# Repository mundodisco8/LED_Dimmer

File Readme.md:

# Gruffalo Fairy Light Dimmer

A simple LED light dimmer. My kids love fairy lights, but the ones we have are too bright to use them as sleep lights so I thought about churning up a quick PWM dimmer for them.

It's a simple project with simple goals:

* Do some electronics. I won't get the Noble prize on electronics for this one.
  * Subgoal: doing something in the incredibly sexy [After Dark](https://blog.oshpark.com/2019/10/10/introducing-our-after-dark-black-fr-4-service/) finish from OSH Park.
* Play with the Silicon Labs toolchain. I don't have any FW on my Github.
* Work with encoders. They are tactile and they are nice!
* Think a bit on user interfaces that children can use.
* See how far I can get without getting sued for copyright infringement.

The design acts as a motherboard for another of my projects, a [breakout board for the BGM220P BLE Module](https://github.com/mundodisco8/BGM220P-Breakout).

This is more or less how it looks like. The renders are done with pcb2blender, and it doesn't handle transparent soldermasks yet, so it's not showing the underlying copper base.

## Working with this project.

It has two elements:

* The hardware is included as a KiCad project. All the files needed are in the `hardware` folder. Make sure you read the [`Readme.md`](hardware/Readme.md) file present there if you want to open it or modify something.
* The firmware is provided as a Simplicity Studio project (Silicon Labs' IDE). You can find it in the `src` folder. Like the HW project, check the [`Readme.md`](src/readme.md) file to get more details about it.

## Tools I'm Using / Stuff I'm Stealing.

Made with:

* KiCad for the HW design, Simplicity Studio / VS Code for the Firmware.
* Unity for unit testing.
* Inkscape, for the art manipulation.
* Fusion360, for 3D model generation, as a source for my Fab layers and for the enclosure.
* Blender + [pcb2blender](https://github.com/30350n/pcb2blender), to generate my renders.
* I'm using [KiBot](https://github.com/INTI-CMNB/KiBot) as the main tool in my CI/CD pipeline.
* I used the Pacifico font in some text elements in the PCB ([link](https://fonts.google.com/specimen/Pacifico))

Things I definitely didn't do:

* The art, taken from [certain children's book authors](https://www.gruffalo.com/).

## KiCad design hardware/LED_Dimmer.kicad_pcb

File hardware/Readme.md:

# Readme

## LED Dimmer PCB

List of things that are interesting to know in order to work with this project.

* This commit uses KiCad 8.0.5
* It uses an unusual font for some text elements. It's Pacifico ([can be obtained here](https://fonts.google.com/specimen/Pacifico), and a copy is left in the `resources/fonts` folder as KiBot needs it).

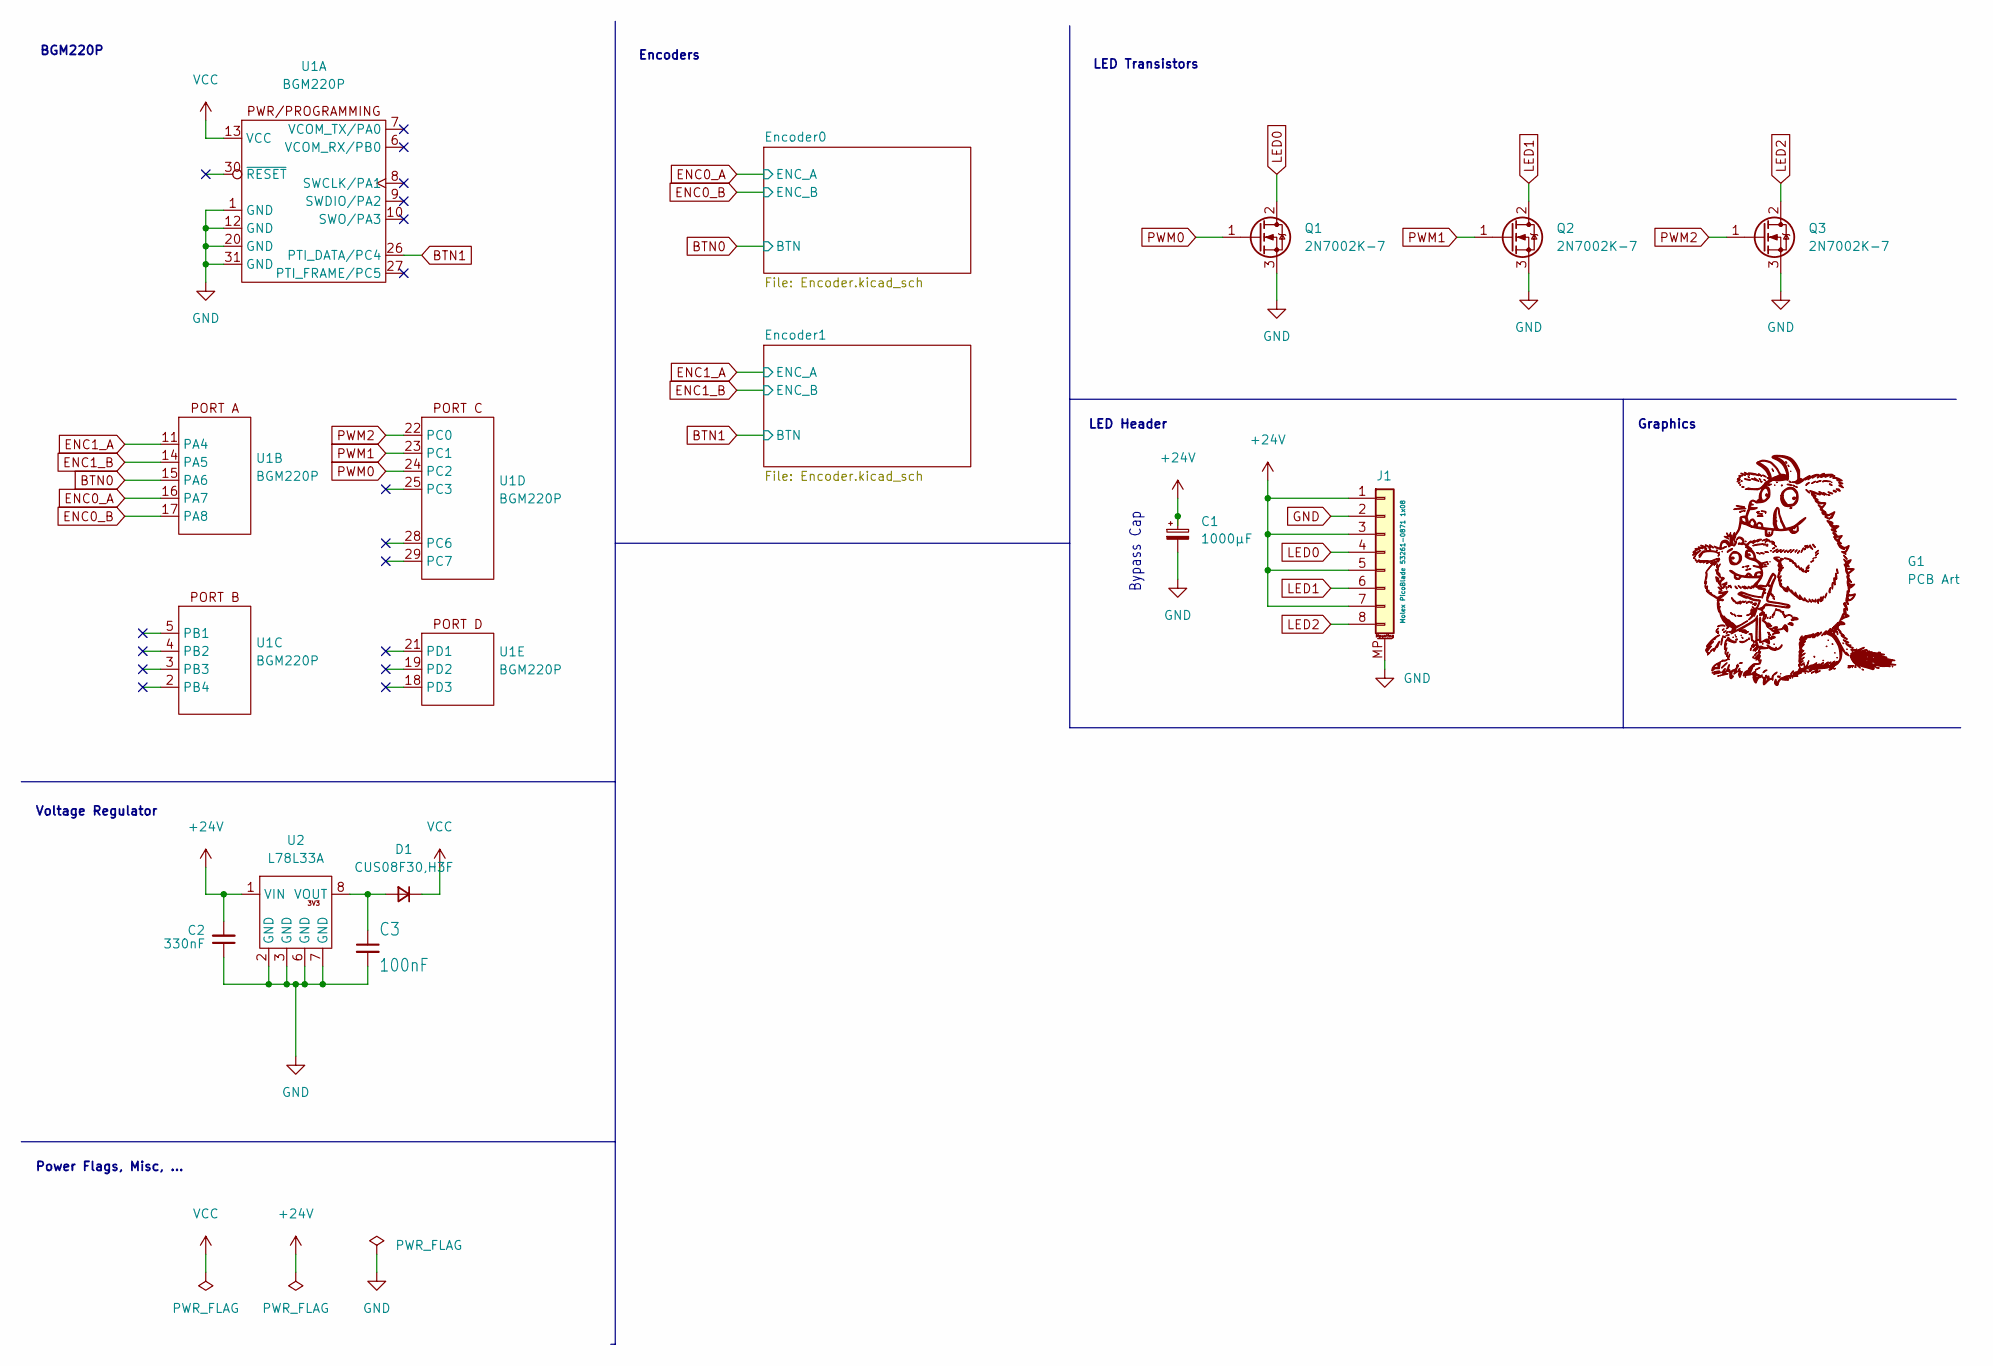
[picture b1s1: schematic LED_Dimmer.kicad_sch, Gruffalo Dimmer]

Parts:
C1: 1000μF; Electrolytic Cap - ⌀16mm, h17mm - SMD - Handsolder; Tolerance ±20%; MPN 865080663020; Digikey PN 732-8465-1-ND
C2: 330nF; 0805-C_Handsolder; Tolerance X7R; MPN 3369310; Digikey PN 1276-1123-1-ND
C3: 100nF; 0603-1.6x0.8mm-C_Handsolder; Tolerance X7R; MPN CL10B104KB8NNWC; Digikey PN 1276-1935-1-ND
D1: CUS08F30,H3F; D_SOD-323_HandSoldering; MPN CUS08F30,H3F; Digikey PN CUS08F30H3FCT-ND
G1: PCB Art; Gruffalo_Art
J1: Molex PicoBlade 53261-0871 1x08; Receptacle - Molex PicoBlade - SMD Right Angle 1x08; MPN 532610871; Digikey PN WM7626CT-ND
Q1, Q2, Q3: 2N7002K-7; SOT-23 - NMOS - GDS; MPN 2N7002K-7; Digikey PN 2N7002K-7DICT-ND
U1: BGM220P; BGM220P_Header_SMD; MPN BGM220PC22WGA; Digikey PN 336-BGM220PC22WGA2-ND
U2: L78L33A; SO-8 - 6x4.9mm p1.27mm - L78L33A - ST; MPN L78L33ACD13TR; Digikey PN 497-1199-1-ND

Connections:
+24V: C1.1, C2.2, J1.1, J1.3, J1.5, J1.7, U2.1 (VIN)
BTN0: U1.15 (PA6); also elsewhere on the board
BTN1: U1.26 (PTI_DATA/PC4); also elsewhere on the board
ENC0_A: U1.16 (PA7); also elsewhere on the board
ENC0_B: U1.17 (PA8); also elsewhere on the board
ENC1_A: U1.11 (PA4); also elsewhere on the board
ENC1_B: U1.14 (PA5); also elsewhere on the board
GND: C1.2, C2.1, C3.2, J1.2, J1.MP (MountPin), Q1.3 (S), Q2.3 (S), Q3.3 (S), U1.1 (GND), U1.12 (GND), U1.20 (GND), U1.31 (GND), U2.2 (GND), U2.3 (GND), U2.6 (GND), U2.7 (GND); also elsewhere on the board
LED0: J1.4, Q1.2 (D)
LED1: J1.6, Q2.2 (D)
LED2: J1.8, Q3.2 (D)
unnamed: C3.1, D1.2 (A), U2.8 (VOUT)
PWM0: Q1.1 (G), U1.24 (PC2)
PWM1: Q2.1 (G), U1.23 (PC1)
PWM2: Q3.1 (G), U1.22 (PC0)
VCC: D1.1 (K), U1.13 (VCC); also elsewhere on the board

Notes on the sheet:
Power Flags, Misc, ...
Voltage Regulator
Encoders
BGM220P
Bypass Cap
LED Transistors
LED Header
Graphics

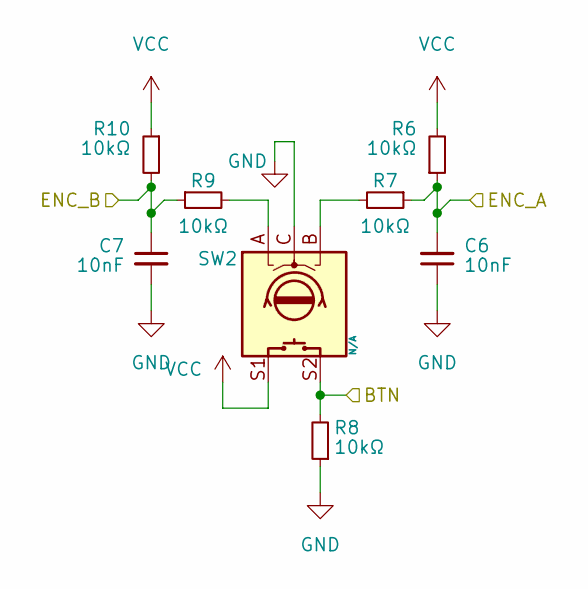
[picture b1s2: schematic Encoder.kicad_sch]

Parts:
C6, C7: 10nF; 0603-1.6x0.8mm-C_Handsolder; Tolerance X7R; MPN CL10B103KB8NNNC; Digikey PN 1276-1009-1-ND
R6, R7, R8, R9, R10: 10kΩ; 0805-R_Handsolder; MPN RC0805JR-0710KL; Digikey PN 311-10KARCT-ND
SW2: N/A; Rotary Encoder - PEC11R - ∅11mm; MPN PEC11R-4115F-S0018; Digikey PN PEC11R-4115F-S0018-ND

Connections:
BTN1: R8.2, SW2.S2; also elsewhere on the board
ENC1_A: C6.2, R6.1, R7.1; also elsewhere on the board
ENC1_B: C7.1, R9.1, R10.2; also elsewhere on the board
GND: C6.1, C7.2, R8.1, SW2.C; also elsewhere on the board
unnamed: R7.2, SW2.B
unnamed: R9.2, SW2.A
VCC: R6.2, R10.1, SW2.S1; also elsewhere on the board

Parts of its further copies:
C4, C5: 10nF; 0603-1.6x0.8mm-C_Handsolder; Tolerance X7R; MPN CL10B103KB8NNNC; Digikey PN 1276-1009-1-ND
R1, R2, R3, R4, R5: 10kΩ; 0805-R_Handsolder; MPN RC0805JR-0710KL; Digikey PN 311-10KARCT-ND
SW1: N/A; Rotary Encoder - PEC11R - ∅11mm; MPN PEC11R-4115F-S0018; Digikey PN PEC11R-4115F-S0018-ND

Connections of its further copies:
BTN0: R3.2, SW1.S2; also elsewhere on the board
ENC0_A: C4.2, R1.1, R2.1; also elsewhere on the board
ENC0_B: C5.1, R4.1, R5.2; also elsewhere on the board
GND: C4.1, C5.2, R3.1, SW1.C; also elsewhere on the board
unnamed: R2.2, SW1.B
unnamed: R4.2, SW1.A
VCC: R1.2, R5.1, SW1.S1; also elsewhere on the board

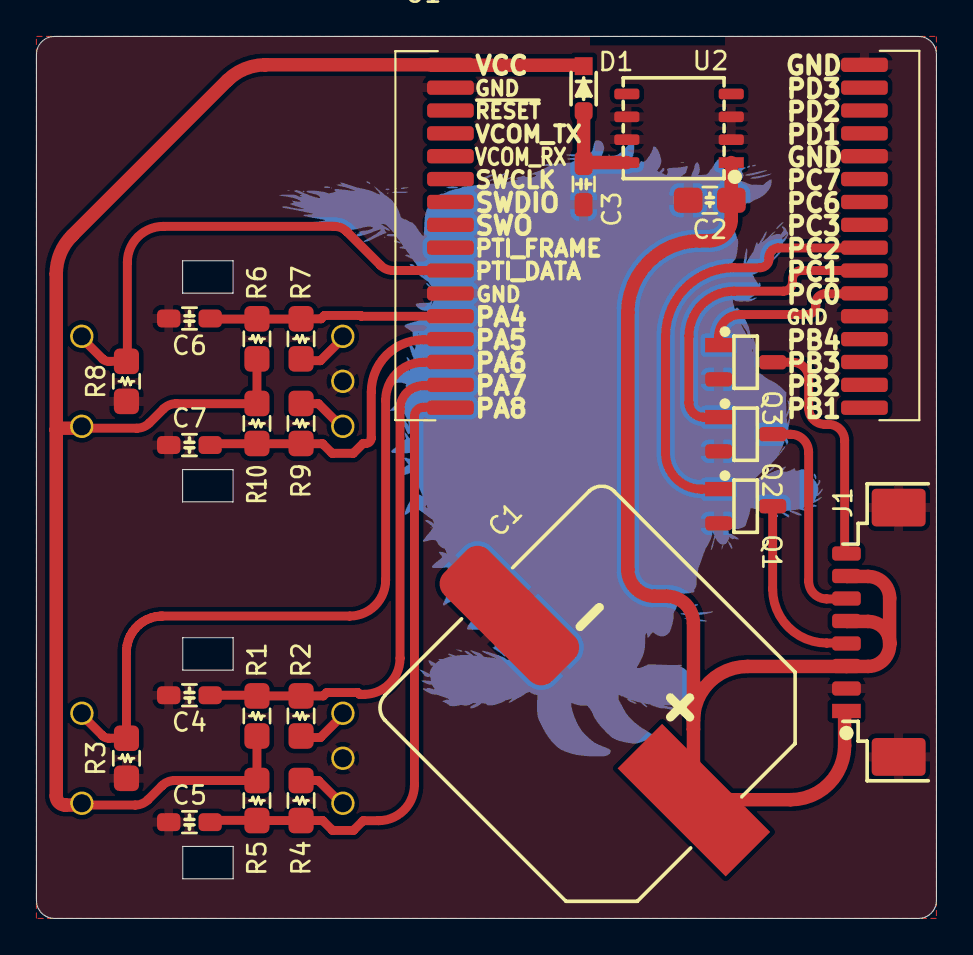
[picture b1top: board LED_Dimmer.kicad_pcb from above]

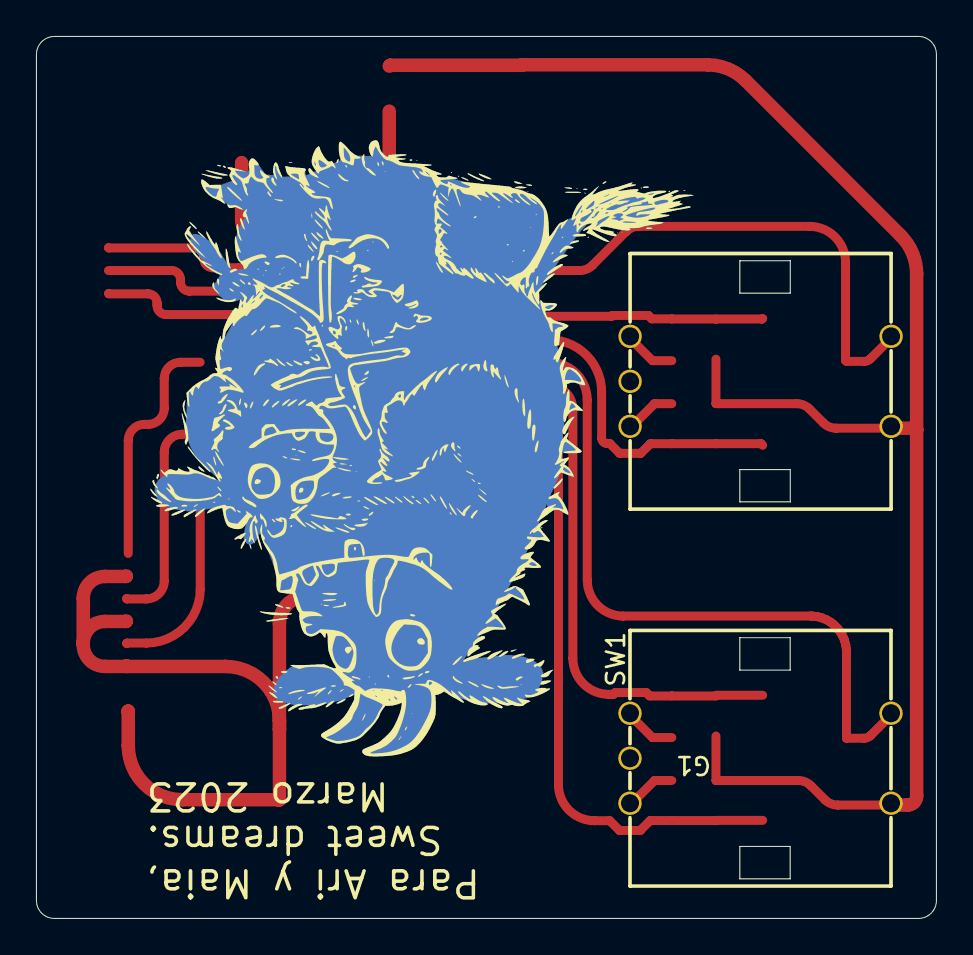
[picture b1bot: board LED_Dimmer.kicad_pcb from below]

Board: 2 copper layers, 50.0 x 49.0 mm, 27 parts (3 on the bottom side), 20 nets.

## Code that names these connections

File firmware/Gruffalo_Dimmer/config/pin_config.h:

#ifndef PIN_CONFIG_H
#define PIN_CONFIG_H

// $[CMU]
// [CMU]$

// $[LFXO]
// [LFXO]$

// $[PRS.ASYNCH0]
// [PRS.ASYNCH0]$

// $[PRS.ASYNCH1]
// [PRS.ASYNCH1]$

// $[PRS.ASYNCH2]
// [PRS.ASYNCH2]$

// $[PRS.ASYNCH3]
// [PRS.ASYNCH3]$

// $[PRS.ASYNCH4]
// [PRS.ASYNCH4]$

// $[PRS.ASYNCH5]
// [PRS.ASYNCH5]$

// $[PRS.ASYNCH6]
// [PRS.ASYNCH6]$

// $[PRS.ASYNCH7]
// [PRS.ASYNCH7]$

// $[PRS.ASYNCH8]
// [PRS.ASYNCH8]$

// $[PRS.ASYNCH9]
// [PRS.ASYNCH9]$

// $[PRS.ASYNCH10]
// [PRS.ASYNCH10]$

// $[PRS.ASYNCH11]
// [PRS.ASYNCH11]$

// $[PRS.SYNCH0]
// [PRS.SYNCH0]$

// $[PRS.SYNCH1]
// [PRS.SYNCH1]$

// $[PRS.SYNCH2]
// [PRS.SYNCH2]$

// $[PRS.SYNCH3]
// [PRS.SYNCH3]$

// $[GPIO]
// GPIO EM4WU7 on PC05
#ifndef GPIO_EM4WU7_PORT                        
#define GPIO_EM4WU7_PORT                         SL_GPIO_PORT_C
#endif
#ifndef GPIO_EM4WU7_PIN                         
#define GPIO_EM4WU7_PIN                          5
#endif

// GPIO EM4WU8 on PC07
#ifndef GPIO_EM4WU8_PORT                        
#define GPIO_EM4WU8_PORT                         SL_GPIO_PORT_C
#endif
#ifndef GPIO_EM4WU8_PIN                         
#define GPIO_EM4WU8_PIN                          7
#endif

// [GPIO]$

// $[TIMER0]
// TIMER0 CC0 on PB01
#ifndef TIMER0_CC0_PORT                         
#define TIMER0_CC0_PORT                          SL_GPIO_PORT_B
#endif
#ifndef TIMER0_CC0_PIN                          
#define TIMER0_CC0_PIN                           1
#endif

// TIMER0 CC1 on PB02
#ifndef TIMER0_CC1_PORT                         
#define TIMER0_CC1_PORT                          SL_GPIO_PORT_B
#endif
#ifndef TIMER0_CC1_PIN                          
#define TIMER0_CC1_PIN                           2
#endif

// TIMER0 CC2 on PB03
#ifndef TIMER0_CC2_PORT                         
#define TIMER0_CC2_PORT                          SL_GPIO_PORT_B
#endif
#ifndef TIMER0_CC2_PIN                          
#define TIMER0_CC2_PIN                           3
#endif

// [TIMER0]$

// $[TIMER1]
// [TIMER1]$

// $[TIMER2]
// [TIMER2]$

// $[TIMER3]
// [TIMER3]$

// $[TIMER4]
// [TIMER4]$

// $[USART0]
// [USART0]$

// $[USART1]
// [USART1]$

// $[I2C1]
// [I2C1]$

// $[PDM]
// [PDM]$

// $[LETIMER0]
// [LETIMER0]$

// $[IADC0]
// [IADC0]$

// $[I2C0]
// [I2C0]$

// $[EUART0]
// EUART0 RX on PB00
#ifndef EUART0_RX_PORT                          
#define EUART0_RX_PORT                           SL_GPIO_PORT_B
#endif
#ifndef EUART0_RX_PIN                           
#define EUART0_RX_PIN                            0
#endif

// EUART0 TX on PA00
#ifndef EUART0_TX_PORT                          
#define EUART0_TX_PORT                           SL_GPIO_PORT_A
#endif
#ifndef EUART0_TX_PIN                           
#define EUART0_TX_PIN                            0
#endif

// [EUART0]$

// $[PTI]
// [PTI]$

// $[MODEM]
// [MODEM]$

// $[CUSTOM_PIN_NAME]
#ifndef _PORT                                   
#define _PORT                                    SL_GPIO_PORT_A
#endif
#ifndef _PIN                                    
#define _PIN                                     0
#endif




#ifndef LED1_PORT                               
#define LED1_PORT                                SL_GPIO_PORT_A
#endif
#ifndef LED1_PIN                                
#define LED1_PIN                                 4
#endif

#ifndef LED2_PORT                               
#define LED2_PORT                                SL_GPIO_PORT_A
#endif
#ifndef LED2_PIN                                
#define LED2_PIN                                 5
#endif

#ifndef quad1_0_PORT                            
#define quad1_0_PORT                             SL_GPIO_PORT_A
#endif
#ifndef quad1_0_PIN                             
#define quad1_0_PIN                              6
#endif

#ifndef quad1_1_PORT                            
#define quad1_1_PORT                             SL_GPIO_PORT_A
#endif
#ifndef quad1_1_PIN                             
#define quad1_1_PIN                              7
#endif



#ifndef PWM2_PORT                               
#define PWM2_PORT                                SL_GPIO_PORT_B
#endif
#ifndef PWM2_PIN                                
#define PWM2_PIN                                 1
#endif

#ifndef PWM1_PORT                               
#define PWM1_PORT                                SL_GPIO_PORT_B
#endif
#ifndef PWM1_PIN                                
#define PWM1_PIN                                 2
#endif

#ifndef PWM0_PORT                               
#define PWM0_PORT                                SL_GPIO_PORT_B
#endif
#ifndef PWM0_PIN                                
#define PWM0_PIN                                 3
#endif





#ifndef quad0_0_PORT                            
#define quad0_0_PORT                             SL_GPIO_PORT_C
#endif
#ifndef quad0_0_PIN                             
#define quad0_0_PIN                              3
#endif

#ifndef LED0_PORT                               
#define LED0_PORT                                SL_GPIO_PORT_C
#endif
#ifndef LED0_PIN                                
#define LED0_PIN                                 4
#endif

#ifndef btn1_PORT                               
#define btn1_PORT                                SL_GPIO_PORT_C
#endif
#ifndef btn1_PIN                                
#define btn1_PIN                                 5
#endif

#ifndef quad0_1_PORT                            
#define quad0_1_PORT                             SL_GPIO_PORT_C
#endif
#ifndef quad0_1_PIN                             
#define quad0_1_PIN                              6
#endif

#ifndef btn0_PORT                               
#define btn0_PORT                                SL_GPIO_PORT_C
#endif
#ifndef btn0_PIN                                
#define btn0_PIN                                 7
#endif




// [CUSTOM_PIN_NAME]$

#endif // PIN_CONFIG_H

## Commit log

2020-10-30 Init Repo
2020-10-30 Added HW. First Spin at OSH Park
2020-10-30 First FW Commit
2020-10-31 Started Readme.md
2022-11-08 Empty Project with debug logging
2022-11-11 Basic handling of one rotary encoder via interrutps
2022-11-18 Working buttons and rotary encoder with debouncing for the buttons and as much as possible unit tested!
2022-11-18 VS Code stuff. I'm the only one working on this, so no need to remove it
2022-11-18 Tests viewable in VS Code!
2022-11-22 App with buttons working (only encoder 1). 100% unit tested
2022-11-27 Extracted types defined by the *_HW headers to their own .h files, now they can be included in other headers for function declaration without making testing impossible!! First stab at generating and 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
2022-12-08 WIP Unit testing what we have so far to link to Ceedling issue in github
2023-02-10 Updated HW to KiCad. Most Done, only graphics left
2023-02-10 WIP - Made lots of changes, then didn't commit for 2 months, and deleted the project. Had to restore from sharepoint. I think I'm back to where I was. At least test run and the project compiles. Big 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
2023-03-02 v2 Board Ready - Added Art - Removed DRC/ERC - Finished BOM
2023-03-02 PCB art
2023-06-28 Getting ready for KiBot. Removed some old references to 3D models from some parts
2023-07-03 Changed the 3D model of the diode to an externally-added STEP file Removed Refs from potentiometers
2023-10-22 Not sure of the complete list of changes, but fixed a bunch of DRC/ERC errors
2023-10-23 CI/CD set up
2023-10-23 Enable CICD on HW branch
2023-10-23 fixes CI/CD
2023-10-23 Minor fix: forgot to update model after changing 3D model
2023-10-23 remove some warnings and errors from CICD
2023-10-23 Diagnosing missing fonts
2023-10-23 This should complete the CICD steps
2023-10-24 Added a readme
2023-10-24 Changed a digikey PN and removed the gruffalo art from the BOM
2023-10-26 Ready to merge
2023-11-08 Cosmetic changes, moved text on silk to copper+mask Added KiCost Kibot Action
2023-11-08 Fix CI/CD
2023-11-10 Test SSH into CICD
2023-11-10 Added some parts to the BoM that are not on the board (connector receptacle, crimps) Checked status of MPNs, and removed some old ones
2023-11-10 Removed the ssh session from Github Actions
2023-11-10 Continuous Integration Build Artifacts
2023-11-16 Added generation of a bottom image to use as texture in Fusion Changed font
2024-09-13 Updated HW Files to KiCad 8.0
2024-09-17 Updated FW Project to Simplicity SDK 2024.6.1
2024-09-19 Added the SDK files to the project, as they were just linked before
2024-09-19 Cleared all the warnings in the project
2024-09-19 Reenabled the FEM (didn't need to disable, it seems)
2024-09-25 Latest WIP, still stuck in RTCC_SyncWait()
2024-09-27 FW works again. Restarted from an EmptySoC again, and code now runs properly
2024-09-27 WIP, found the timer overflow error, working on it
2024-10-04 WIP Changed timer struct to incomplete type to fix overflow
2024-10-18 Buttons work now, but quad doesn't. Need to check the HW Updated Ceedling to latest version, tests are now passing!
2024-10-23 Renamed some functions that are generic and not need a pin number on them
2024-10-23 Working again!
    Got quad0 to work again! need some research on quad1
2024-10-31 Moved "percentage" to int
    To avoid weird cases where negatives roll to 255
2024-10-31 Formatting changes
2024-11-15 Got PWM working in the three channels
    Not entirely happy with things, need to clean a bit and change the way the next count is fed to the CC module, but it works!
2024-11-22 Wrapped some SDK calls
2024-11-22 Tests pass, although I had to disable some until I get some feedback from the Ceedling people
2024-11-24 Increased a bit the test coverage
2024-11-27 Tidied up the way channel count values are passed around
2024-11-27 Coverage at 100%
2024-11-27 Cleared silly warning
2024-11-29 Hotfix: Bug enabling timers
2024-11-30 Added LongPress!
2025-11-24 Updated the art a bit
2025-11-24 Updated to KiCad 9
    - Changed LED Connectors to Kyocera
    - Made board bigger
    - Made art better and bigger
    - Micro breakout now has header pins outside (easier to solder)
2025-11-26 Fixed two 3d models that were not exporting properly
2025-12-04 99% there
    Board is almost ready for new spin, but a couple of bugs exporting the 3D model of the board require custom 3D models and I'm not superhappy with that. Waiting for them to get fixed, but might take m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
2025-12-11 KiBot Config Udpdated to KiCad9
2025-12-12 Change SDK files
2026-01-16 Updated to SS6 / SDK 2025.6.2
2026-01-16 Formatted Code
2026-01-21 Added testing
2026-02-03 Fixed Generators in VSCode
2026-02-03 Project Compiles
2026-02-03 Updated SDK to 2025.12.0
2026-02-05 More problems with SDK, hopefully solved?
2026-02-08 Fixed Brightness Looks Good!
2026-02-11 Refactored Brightness
2026-02-11 Test Coverage
2026-02-13 Moved to a pre-calculated LUT and a simpler brightness control
2026-02-13 Button 1 changes animation mode
2026-02-15 Linked LEDs to PWM channels, instead of relying on a function to get it
2026-02-16 Moved to Up-Down, as I think it will work better. Fixed interrupts as I was using the wrong ones as drivers
2026-02-16 Breathe at fixed period and brightness
2026-02-16 Typo
2026-02-16 Working on tests
2026-02-17 Can change breathe effect period with encoder (plus added asserts to tests)
2026-02-18 Breathe Effect Brightness can be adjusted
2026-02-18 Increased test coverage
2026-02-18 Docs
2026-02-19 Normalised line endings?
2026-02-20 Connected buttons to EM4 wake up pins
2026-02-26 Refactored to one single function to start timers to reduce code duplication
2026-02-26 Refactored Debounce to use one clock
2026-02-27 And more refactoring! debounce shouldn't be starting and stopping button timers
2026-03-04 Added Kyocera Connector
2026-03-04 Updated Rotary Encoder 3d Model
2026-03-05 Improved GPIO and added set pin for EM4 wake
2026-03-05 Probably Enables EM4
2026-03-09 Tweaked positions of encoders, smd passive shapes, and rerouted
2026-03-09 EM4 Working
2026-03-10 Added animation type setter and getter
2026-03-10 Added NVM recovery on EM4 entry
2026-03-10 Doc Update
2026-03-10 Forgot to add this bit
2026-03-10 Some test warnings removed
2026-03-10 CppCheck
2026-03-11 Proper way to turn LEDS off before entering sleep
2026-03-11 Added an "all channels" selector to set properties on all channels at once
2026-03-12 cppCheck Passing
2026-03-13 Documentation
2026-03-13 Testing 100%!
2026-03-16 Changed board origin to centre of pcb
2026-03-18 Added LED Indicators
2026-03-23 Some FW files that escaped...
2026-03-23 Re-Enable ERC-DRC in config file
2026-03-24 Not sure what I did here ¯\_(ツ)_/¯
2026-03-24 Added LED indicator pins
2026-03-24 Changes for LED indicator
2026-03-25 LED Channel Selected Indicators
2026-04-14 Regulator pinout was wrong! Also decoupling cap was not decoupling
2026-04-14 CICD Changes
2026-04-14 Upload coverage history
2026-04-14 more updates
